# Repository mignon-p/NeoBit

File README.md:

# neo:bit

The neo:bit is a board which attaches to the [edge connector][11] of
the [BBC micro:bit][16] and provides:

* Two slide potentiometers, connected to micro:bit pins P1 and P2,
  which can be read as analog inputs.

* A terminal block for connecting "[NeoPixels][92]" (WS-2812 LEDs),
  with a level shifter to convert from 3.3V logic (on pin P16) to 5V
  logic.

* A terminal block for connecting "[DotStars][93]" (APA-102 LEDs),
  with a level shifter to convert from 3.3V logic (on pins P13 and
  P15) to 5V logic.

* A [Qwiic][89] connector for attaching I2C peripherals.

* A 3.5mm audio jack for headphones.  (Connected to pin P0).

* A barrel connector for an external 5-12V power supply, which is
  mandatory for powering the NeoPixels, and can also optionally
  backpower the micro:bit safely.

This repository contains [KiCad][83] and [gerber][84] files for the
neo:bit board.

* [View schematic](doc/schematic.pdf)
* [View PCB][30]

## Usage

### Power

Note that the voltage which comes in on the barrel jack is used
directly to power the NeoPixels and DotStars, so you need to choose a
voltage which is appropriate for the NeoPixels and/or DotStars you are
using.  Most NeoPixels are 5V, although there are a few
[12V ones][90].  I don't know of any DotStars which are not 5V.  You
can't have a different voltage for the NeoPixels and the DotStars.

The neo:bit contains a low-dropout 3.3V voltage regulator, which is
used for back-powering the micro:bit, and for supplying the 3.3V power
on the Qwiic connector.  You probably shouldn't draw more than 90 mA
on the Qwiic connector's power pin.

The neo:bit also contains a low-dropout 5V voltage regulator, but that
is just to supply the 5V signal on the NeoPixel and DotStar data
lines.

### Potentiometers

To read the slide potentiometers, just configure P1 and P2 as analog
inputs, and read them.  The idea is that you could use these inputs to
control your NeoPixel animation, such as the speed, color, or
brightness.

### NeoPixels

J4 has the NeoPixel output, along with +V and GND.  You may want to
connect a [JST-SM pigtail][80] to the J4 screw terminals.  This will
let you connect strings of 5V NeoPixels, such as ones from
[Alitove][19] or [Wesiri][81], or my
[chainable NeoPixel butterflies][20].  (The Wesiri lights come with
the necessary pigtail, so you don't need to buy one separately.)

You must have an external power supply (such as [this one][23] or
[this one][24] for 5V, or [this one][91] for 12V) connected to the
neo:bit's barrel jack in order to power the NeoPixels.  If the
external power supply is connected, the neo:bit will also supply 3.3V
back to the micro:bit, so it is not necessary to power the micro:bit
from another source.  (However, this is done with a protection diode,
so it is OK to have the micro:bit connected to another source at the
same time the external supply is connected.)  If you only want to use
the potentiometers and/or Qwiic but not the NeoPixel output or DotStar
output, then you do not need to have an external supply connected, as
long as the micro:bit is powered by another source.

Following the [NeoPixel best practices][25], the neo:bit includes a
470 ohm resistor on the NeoPixel data line, and there is a 1000µF
capacitor on the +V power line.

Once you have your NeoPixels hooked up, you should be able to access
them by instantiating a NeoPixel strip on pin P16 in either
[MakeCode][27] or [Python][28].  The Alitove and Wesiri strings, as
well as my NeoPixel butterflies, use RGB order instead of the default
GRB order.

### Qwiic

I have [an example](https://makecode.microbit.org/_DCHeKoPCWEWu) for
how to use the [Qwiic Keypad](https://www.sparkfun.com/products/14836),
and [another example](https://makecode.microbit.org/_4x4iFTWd7JoU) for
how to use the [Qwiic Joystick](https://www.sparkfun.com/products/14656).

## Ordering the Board

You can order this board [directly from OSH Park][29] without needing
to upload anything.

Or, if you prefer to go with another fab like [Elecrow][86] or
[JLCPCB][87], all you need to do is zip up the files in the `gerber`
directory, and upload that zip file to the fab.

If you want to modify the design, the source is provided in
[KiCad][83] format.

## Bill of Materials

| Ref      | Description                      | MPN                 | Digi-Key PN                  |
| -------- | -------------------------------- | ------------------- | ---------------------------- |
| C1       | CAP ALUM 1000UF 20% 25V RADIAL   | 25PX1000MEFCT810X16 | [1189-1583-1-ND][C1]         |
| C2       | CAP CER 0.1UF 50V X7R RADIAL     | K104K10X7RF5UH5     | [BC2665CT-ND][C2]            |
| C3-C6    | CAP CER 1UF 50V Y5V RADIAL       | K105Z20Y5VF5TH5     | [BC1168CT-ND][C3]            |
| C7       | CAP ALUM 47UF 20% 16V RADIAL     | ECE-A1CKS470        | [P969-ND][C7]                |
| C8, C9   | CAP ALUM 220UF 20% 10V RADIAL    | UVK1A221MDD1TD      | [493-7455-1-ND][C8]          |
| C10      | CAP CER 10000PF 50V X7R RADIAL   | K103K15X7RF5TL2     | [BC1078CT-ND][C10]           |
| D1       | DIODE SCHOTTKY 20V 1A DO41       | 1N5817              | [1N5817FSCT-ND][D1]          |
| J1       | CONN JACK STEREO 3.5MM R/A       | SJ1-3533NG          | [CP1-3533NG-ND][J1]          |
| J2       | CONN PWR JACK 2X5.5MM SOLDER     | PJ-063AH            | [CP-063AH-ND][J2]            |
| J3       | Qwiic JST Connector - SMD 4-pin  | [PRT-14417][J3]     | (SparkFun)                   |
| J4       | TERM BLOCK 4POS SIDE ENT 3.5MM   | 1776275-4           | [A98038-ND][J4]              |
| J5       | micro:bit through-hole right-angle edge connector | [3342][J5] | (Adafruit)           |
| J6       | TERM BLOCK 3POS SIDE ENT 3.5MM   | 1776275-3           | [A98037-ND][J6]              |
| R1       | RES 100 OHM 1/4W 5% AXIAL        | CF14JT100R          | [CF14JT100RCT-ND][R1]        |
| R2       | RES 470 OHM 1/4W 5% AXIAL        | CF14JT470R          | [CF14JT470RCT-ND][R2]        |
| R3       | RES 22 OHM 1/4W 5% AXIAL         | CF14JT22R0          | [CF14JT22R0CT-ND][R3]        |
| RV1, RV2 | SLIDE POT 10K OHM 0.25W TOP 45MM | PTA4553-2015CPB103  | [PTA4553-2015CPB103-ND][RV1] |
| U1       | IC BUF NON-INVERT 5.5V 14DIP     | SN74AHCT125N        | [296-4655-5-ND][U1]          |
| U2       | IC REG LINEAR 3.3V 250MA TO92-3  | MCP1702-3302E/TO    | [MCP1702-3302E/TO-ND][U2]    |
| U3       | IC REG LINEAR 5V 250MA TO92-3    | MCP1702-5002E/TO    | [MCP1702-5002E/TO-ND][U3]    |
| (qty 2)  | KNOB SMOOTH 0.157 X 0.039" NYLON | 1300-E              | [1722-1329-ND][61]           |

Plus you'll need a micro:bit, a power supply (such as [this one][82]),
and some NeoPixels.

The right-angle micro:bit edge connector (J5) is 4UCON 10156, which is
available from [Adafruit][J5] in the US and from [Cool Components][26]
in the UK.

## Assembly

Most of the assembly should be straightforward, but there are a few
connectors worthy of more discussion.

### Qwiic connector

The four electrical pins are not enough to hold this connector in
place.  There are two mounting pins which are also meant to be
soldered, but I found hand-soldering them was nearly impossible.  So,
I used a drop of epoxy to hold the Qwiic connector in place.

### Terminal blocks

I've found that stranded wires don't stay in the terminal blocks very
well, so I recommend using solid wire.  Or, you may wish to omit the
terminal blocks entirely and solder wires directly to the board.

### micro:bit connector

The micro:bit connector has 80 pins, but only 40 of them need to be
soldered.  The pins that need to be soldered are the two rows farthest
from the edge.  (These pins are slightly taller than the others.)  I
usually solder just a few of the pins on the row closest to the edge,
too, just for mechanical stability.

## License

The files in this repo are licensed under [CC-BY-SA 4.0][10].

Some symbols and footprints in this repo are under different licenses:

* [microbit_edge_connector][1] symbol by [anthonykirby][3] and [4UCON_10156_90deg][2] footprint (which I have substantially modified) by [SukkoPera][4] ([MIT License][5]).
* 74AHCT125 symbol is a substantially modified version of the symbol from [a library][6] by [propane-and-electrons][7].
* Barrel_Jack_MountingPin symbol is from [the official KiCad 5 library][8], and R_POT_Mountingpin symbol is derived from a symbol in the official library ([CC-BY-SA 4.0 with exception][9]).
* The TerminalBlock_4Ucon_* footprints are also from the official KiCad 5 library.

[1]: https://github.com/anthonykirby/kicad_microbit_connector/blob/master/lib_microbit_connector/lib_microbit_connector.lib
[2]: https://github.com/SukkoPera/OpenAmiga600RamExpansion/blob/master/OpenAmiga600RamExpansion.pretty/4UCON_10156_90deg.kicad_mod
[3]: https://github.com/anthonykirby
[4]: https://github.com/SukkoPera
[5]: https://github.com/anthonykirby/kicad_microbit_connector/blob/master/LICENSE
[6]: https://github.com/propane-and-electrons/kicad-libs/blob/master/shardy.lib
[7]: https://github.com/propane-and-electrons
[8]: https://github.com/KiCad/kicad-symbols/blob/master/Connector.lib
[9]: https://forum.kicad.info/t/kicad-library-licensing/7856
[10]: https://creativecommons.org/licenses/by-sa/4.0/legalcode
[11]: https://tech.microbit.org/hardware/edgeconnector_ds/
[16]: https://microbit.org/
[17]: https://www.sparkfun.com/products/14165
[18]: https://cdn.sparkfun.com/datasheets/Prototyping/ACCA-1495.pdf
[19]: https://smile.amazon.com/gp/product/B01AG923GI/
[20]: https://github.com/ppelleti/ButterflyChain
[23]: https://www.adafruit.com/product/1466
[24]: https://www.adafruit.com/product/658
[25]: https://learn.adafruit.com/adafruit-neopixel-uberguide/best-practices
[26]: https://coolcomponents.co.uk/products/edge-connector-for-bbc-micro-bit
[27]: https://makecode.microbit.org/pkg/microsoft/pxt-neopixel
[28]: https://microbit-micropython.readthedocs.io/en/latest/neopixel.html
[29]: https://oshpark.com/shared_projects/cOlGXHEk
[30]: https://eyrie.io/board/9e1a5f1d622a41188564be353a699805
[80]: https://www.adafruit.com/product/1663
[81]: https://smile.amazon.com/gp/product/B075T84ZR3/
[82]: https://www.adafruit.com/product/1466
[83]: http://kicad.org/
[84]: https://en.wikipedia.org/wiki/Gerber_format
[86]: https://www.elecrow.com/pcb-manufacturing.html
[87]: https://jlcpcb.com/quote
[89]: https://www.sparkfun.com/qwiic
[90]: https://www.adafruit.com/product/3869
[91]: https://www.adafruit.com/product/352
[92]: https://www.adafruit.com/category/168
[93]: https://www.adafruit.com/category/885

[C1]: https://www.digikey.com/products/en?keywords=1189-1583-1-ND
[C2]: https://www.digikey.com/products/en?keywords=BC2665CT-ND
[C3]: https://www.digikey.com/products/en?keywords=BC1168CT-ND
[C7]: https://www.digikey.com/products/en?keywords=P969-ND
[C8]: https://www.digikey.com/products/en?keywords=493-7455-1-ND
[C10]: https://www.digikey.com/products/en?keywords=BC1078CT-ND
[D1]: https://www.digikey.com/products/en?keywords=1N5817FSCT-ND
[J1]: https://www.digikey.com/products/en?keywords=CP1-3533NG-ND
[J2]: https://www.digikey.com/products/en?keywords=CP-063AH-ND
[J3]: https://www.sparkfun.com/products/14417
[J4]: https://www.digikey.com/products/en?keywords=A98038-ND
[J5]: https://www.adafruit.com/product/3342
[J6]: https://www.digikey.com/products/en?keywords=A98037-ND
[R1]: https://www.digikey.com/products/en?keywords=CF14JT100RCT-ND
[R2]: https://www.digikey.com/products/en?keywords=CF14JT470RCT-ND
[R3]: https://www.digikey.com/products/en?keywords=CF14JT22R0CT-ND
[RV1]: https://www.digikey.com/products/en?keywords=PTA4553-2015CPB103-ND
[U1]: https://www.digikey.com/products/en?keywords=296-4655-5-ND
[U2]: https://www.digikey.com/products/en?keywords=MCP1702-3302E%2FTO-ND
[U3]: https://www.digikey.com/products/en?keywords=MCP1702-5002E%2FTO-ND

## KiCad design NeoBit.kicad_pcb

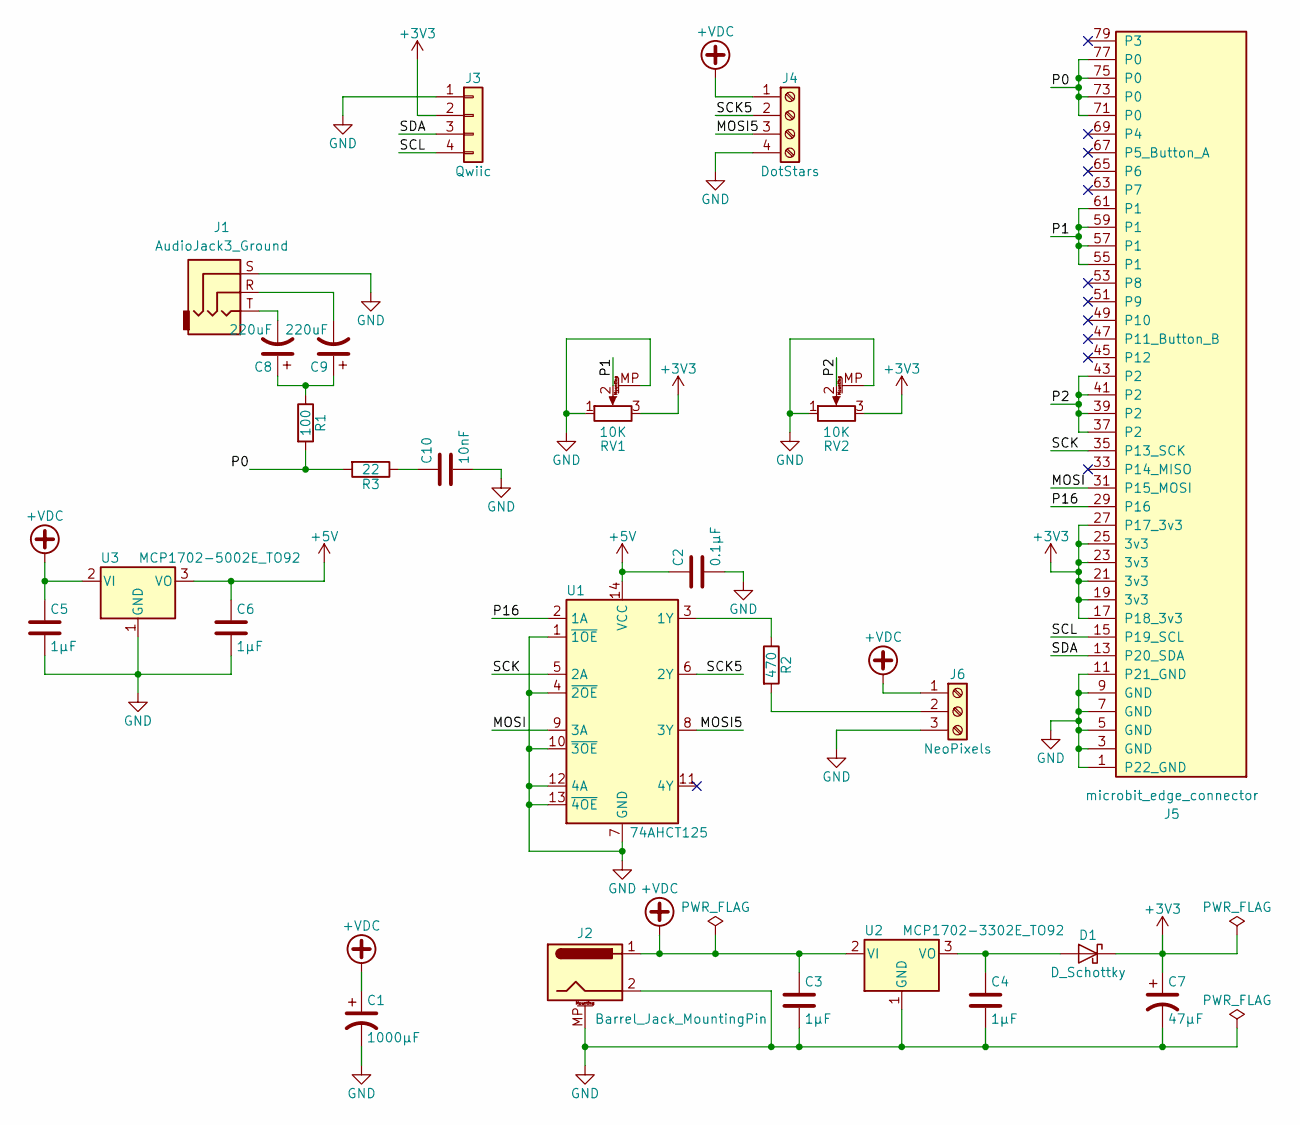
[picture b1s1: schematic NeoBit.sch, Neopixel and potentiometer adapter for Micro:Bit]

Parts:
C1: 1000µF; CP_Radial_D10.0mm_P5.00mm; MPN 25PX1000MEFCT810X16; Digi-Key_PN 1189-1583-1-ND
C2: 0.1µF; C_Rect_L7.0mm_W2.5mm_P5.00mm; MPN K104K10X7RF5UH5; Digi-Key_PN BC2665CT-ND
C3, C4, C5, C6: 1µF; C_Rect_L7.0mm_W2.5mm_P5.00mm; MPN K105Z20Y5VF5TH5; Digi-Key_PN BC1168CT-ND
C7: 47µF; CP_Radial_D6.3mm_P2.50mm; MPN ECE-A1CKS470; Digi-Key_PN P969-ND
C8, C9: 220uF; CP_Radial_D5.0mm_P2.50mm; MPN UVK1A221MDD1TD; Digi-Key_PN 493-7455-1-ND
C10: 10nF; C_Disc_D3.8mm_W2.6mm_P2.50mm; MPN K103K15X7RF5TL2; Digi-Key_PN BC1078CT-ND
D1: D_Schottky; D_DO-41_SOD81_P7.62mm_Horizontal; MPN 1N5817; Digi-Key_PN 1N5817FSCT-ND
J1: AudioJack3_Ground; SJ1-3533NG; MPN SJ1-3533NG; Digi-Key_PN CP1-3533NG-ND
J2: Barrel_Jack_MountingPin; BarrelJack_CUI_PJ-063AH_Horizontal_CircularHoles; MPN PJ-063AH; Digi-Key_PN CP-063AH-ND
J3: Qwiic; JST_SH_SM04B-SRSS-TB_04x1.00mm_Angled; MPN PRT-14417
J4: DotStars; TerminalBlock_4Ucon_1x04_P3.50mm_Vertical; MPN 1776275-4; Digi-Key_PN A98038-ND
J5: microbit_edge_connector; 4UCON_10156_2x40_P1.27mm_Socket_Horizontal; MPN 3342
J6: NeoPixels; TerminalBlock_4Ucon_1x03_P3.50mm_Vertical; MPN 1776275-3; Digi-Key_PN A98037-ND
R1: 100; R_Axial_DIN0207_L6.3mm_D2.5mm_P2.54mm_Vertical
R2: 470; R_Axial_DIN0207_L6.3mm_D2.5mm_P2.54mm_Vertical; MPN CF14JT470R; Digi-Key_PN CF14JT470RCT-ND
R3: 22; R_Axial_DIN0207_L6.3mm_D2.5mm_P2.54mm_Vertical
RV1, RV2: 10K; Bourns_PTA4543; MPN PTA4553-2015CPB103; Digi-Key_PN PTA4553-2015CPB103-ND
U1: 74AHCT125; DIP-14_W7.62mm; MPN SN74AHCT125N; Digi-Key_PN 296-4655-5-ND
U2: MCP1702-3302E_TO92; TO-92_Inline_Narrow_Oval; MPN MCP1702-3302E/TO; Digi-Key_PN MCP1702-3302E/TO-ND
U3: MCP1702-5002E_TO92; TO-92_Inline_Narrow_Oval

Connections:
+3V3: C7.1, D1.1 (K), J3.2, J5.17 (P18_3v3), J5.19 (3v3), J5.21 (3v3), J5.23 (3v3), J5.25 (3v3), J5.27 (P17_3v3), RV1.3, RV2.3
+5V: C2.1, C6.1, U1.14 (VCC), U3.3 (VO)
+VDC: C1.1, C3.1, C5.1, J2.1, J4.1, J6.1, U2.2 (VI), U3.2 (VI)
/MOSI: J5.31 (P15_MOSI), U1.9 (3A)
/MOSI5: J4.3, U1.8 (3Y)
/P0: J5.71 (P0), J5.73 (P0), J5.75 (P0), J5.77 (P0), R1.2, R3.2
/P1: J5.55 (P1), J5.57 (P1), J5.59 (P1), J5.61 (P1), RV1.2
/P2: J5.37 (P2), J5.39 (P2), J5.41 (P2), J5.43 (P2), RV2.2
/P16: J5.29 (P16), U1.2 (1A)
/SCK: J5.35 (P13_SCK), U1.5 (2A)
/SCK5: J4.2, U1.6 (2Y)
/SCL: J3.4, J5.15 (P19_SCL)
/SDA: J3.3, J5.13 (P20_SDA)
GND: C1.2, C2.2, C3.2, C4.2, C5.2, C6.2, C7.2, C10.2, J1.S, J2.2, J2.MP (MountPin), J3.1, J4.4, J5.1 (P22_GND), J5.3 (GND), J5.5 (GND), J5.7 (GND), J5.9 (GND), J5.11 (P21_GND), J6.3, RV1.1, RV1.MP (MountPin), RV2.1, RV2.MP (MountPin), U1.1 (~1OE), U1.4 (~2OE), U1.7 (GND), U1.10 (~3OE), U1.12 (4A), U1.13 (~4OE), U2.1 (GND), U3.1 (GND)
unnamed: C4.1, D1.2 (A), U2.3 (VO)
unnamed: C8.1, C9.1, R1.1
unnamed: C8.2, J1.T
unnamed: C9.2, J1.R
unnamed: C10.1, R3.1
unnamed: J6.2, R2.2
unnamed: R2.1, U1.3 (1Y)

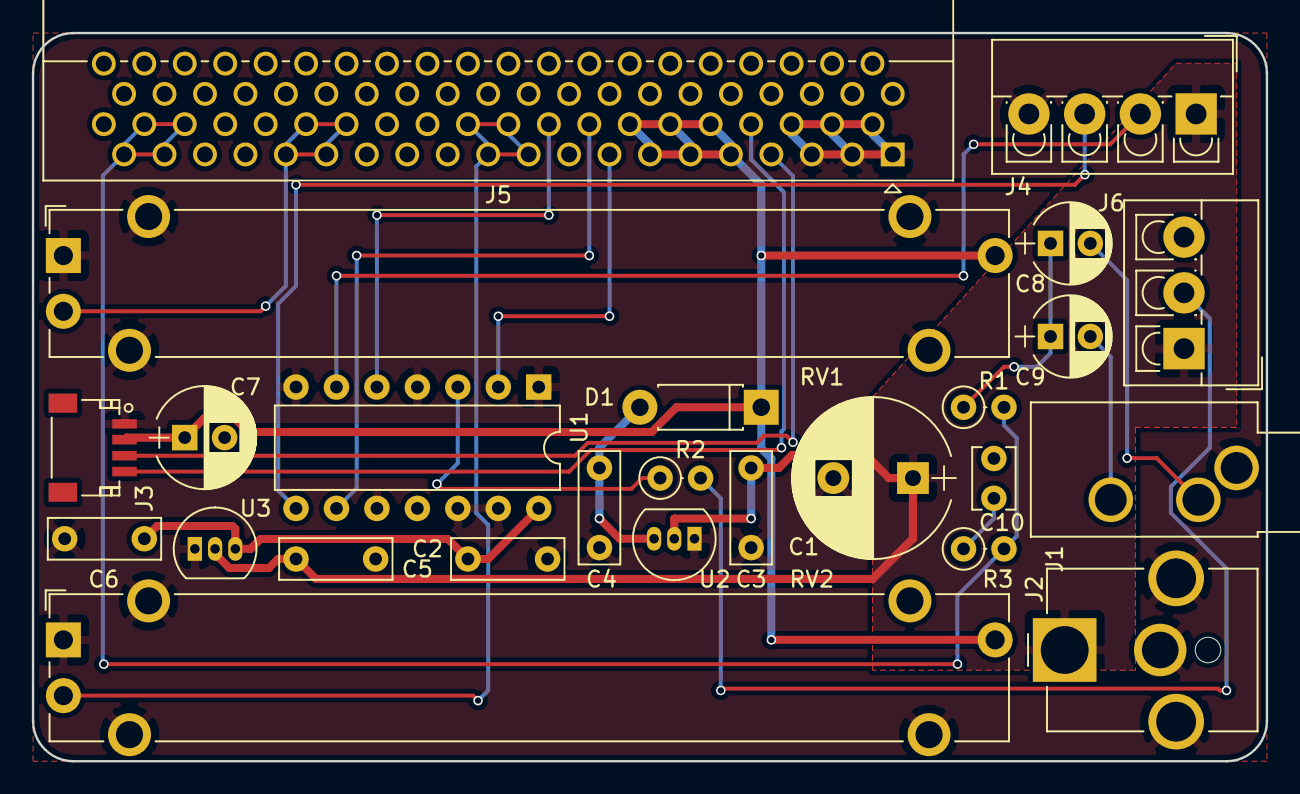
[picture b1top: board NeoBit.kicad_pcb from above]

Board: 2 copper layers, 77.5 x 45.7 mm, 25 parts (0 on the bottom side), 21 nets.

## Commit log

2018-08-30 Initial commit.
2018-08-30 Add component libraries.
2018-08-30 Update pin size and fill of feather components.
2018-08-30 Wire up the micro:bit and feather connectors.
2018-08-30 Add connector for NeoPixels.
2018-08-30 Library with a couple other random components.
2018-08-30 Align 74AHCT125 pins to grid.
2018-08-30 Fix some other issues with symbols.
2018-08-30 Update symbol cache.
2018-08-30 Wired some more things up.
2018-08-30 Add voltage regulator and more.
2018-08-31 Fill in manufacturer part numbers.
2018-08-31 Decrease size of cap on 3.3V supply to 47uF.
2018-08-31 Use correct symbol for microfarads.
2018-08-31 Annotate components.
2018-08-31 Start associating a few footprints.
2018-08-31 Add a couple of footprints.
2018-08-31 Finish footprint associations.
2018-08-31 Started placing footprints.
2018-08-31 Place footprints.
2018-08-31 Tweaks to footprint placement.
2018-08-31 Rounded corners for board outline.
2018-08-31 Board outline.
2018-08-31 5V wiring.
2018-08-31 3V3 wiring.
2018-08-31 Some more tracks.
2018-08-31 I meant for NeoPixel pin to be P0.
2018-08-31 More tracks.
2018-08-31 Finish tracks.
2018-08-31 Fill GND zones.
2018-08-31 Passes DRC now.
2018-08-31 Move one wire to help GND routing a little bit.
2018-08-31 Some stitching vias should help GND.
2018-08-31 One more stitching via.
2018-08-31 Add a couple more stiching vias.
2018-09-01 Add pinout diagram to README.
2018-09-01 I had the pinout for the NeoPixel connector wrong.
    https://cdn.sparkfun.com/datasheets/Prototyping/ACCA-1495.pdf
2018-09-01 Add a couple more stitching vias, although perhaps I am getting carried away.
2018-09-01 Update to new version of micro:bit edge connector footprint.
2018-09-01 NeoBit is based on MicroBitFeather.
2018-09-01 Copy R_POT_MountingPin from R_POT.
2018-09-01 Potentiometer with mounting pin.
2018-09-01 Add potentiometers to schematic.
2018-09-01 Put no-connects on most micro:bit pins.
2018-09-01 Footprint for slide potentiometers.
2018-09-01 Remove old components and tracks.
2018-09-01 Footprints are mostly positioned.
2018-09-01 I don't think we need that cap on 3V3.
2018-09-01 Adjust footprint placement.
2018-09-01 Draw board outline.
2018-09-01 Position text.
2018-09-02 Wire things up.
2018-09-02 Fill zones.
2018-09-03 Add stuff on back silkscreen.
2018-09-03 Add to README.
2018-09-03 Add BOM to README.
2018-09-04 Add silkscreen labels for connectors.
2018-09-04 Added knob to BOM; reformatted table.
2018-09-04 Generate Gerbers.
2018-09-04 Add LICENSE.txt.
2018-09-08 Remove feather library which was inherited from feather:bit.
2018-09-08 Add PDF of schematic.
2018-09-16 Update README and add some pictures.
2018-09-16 Crop photos.
2018-09-16 Links to order board, and view schematic and PCB.
2018-09-20 Added 5V regulator.
2018-09-20 Screw terminals for NeoPixels and DotStars.
2018-09-20 Add symbol for TRS audio jack.
2018-09-20 Add qwiic connector.
2018-09-20 Put audio jack on P0; move NeoPixels to P16.
2018-09-21 Add footprint for CUI SJ1-3533NG audio jack.
2018-09-21 Annotate schematic.
2018-09-21 Don't need this power flag.
2018-09-21 Associate some footprints.
2018-09-21 Add terminal block footprints.
2018-09-21 Associate terminal block footprints.
2018-09-21 Roughly position new footprints.
2018-09-21 Change some part numbers.
2018-09-21 Update audio jack footprint to have pins T, R, and S.
2018-09-21 Add level shifting on DotStar pins.
2018-09-21 Use a higher-voltage capacitor.
2018-09-22 Part numbers for terminal blocks.
2018-09-22 Add 47uF capacitor on 3V3 supply.
2018-09-22 Add capacitor and move labels.
2018-09-22 Extend zones and board outline.
2018-09-22 Change shape of +V zone.
2018-09-22 Get +V zone on correct net.
2018-09-22 Draw a few tracks.
2018-09-22 Added some more tracks.
2018-09-22 Finished wiring power tracks.
2018-09-22 I think I've routed all the tracks.
2018-09-22 Filled zones; passed DRC.
2018-09-22 Start moving some silkscreen around.
2018-09-22 Finish adding silkscreen.
2018-09-22 Metadata.
2018-09-23 Use new footprint for micro:bit edge connector.
2018-09-23 Add filter to audio output.
2018-09-23 Cram audio filter into PCB.
2018-09-23 I had the 220uF capacitors backwards.
2018-09-23 Finish wiring up PCB.
2018-09-23 Passing DRC now.
2018-09-23 Call this 2.0 instead of 1.1; not software compatible.
    NeoPixels changed pin from P0 to P16.
2018-09-23 Regenerate Gerbers.
2018-09-23 Add part numbers for resistors.
2018-09-23 Part number for 5V regulator.
2018-09-25 Update schematic PDF for version 2.0.
2018-09-28 Update README for version 2.0.
2018-09-29 Update BOM in README.
2018-10-02 NeoPixels are now on P16 instead of P0.
2018-10-04 Update README and pictures; add ChangeLog.
2018-10-04 Power line is not necessarily 5V.
2018-10-05 Label the connectors in the neo:bit photo.
2018-10-05 Links for NeoPixels and DotStars.
2018-10-06 Add some additional photos of neo:bit version 2.
2018-10-06 Typo in image URL.
2018-10-14 More comments about terminal blocks.
2018-10-14 Link to Qwiic examples.
2021-10-22 Link to kicad.org
    https://forum.kicad.info/t/warning-avoid-all-links-to-kicad-pcb-org-use-kicad-org/31521
